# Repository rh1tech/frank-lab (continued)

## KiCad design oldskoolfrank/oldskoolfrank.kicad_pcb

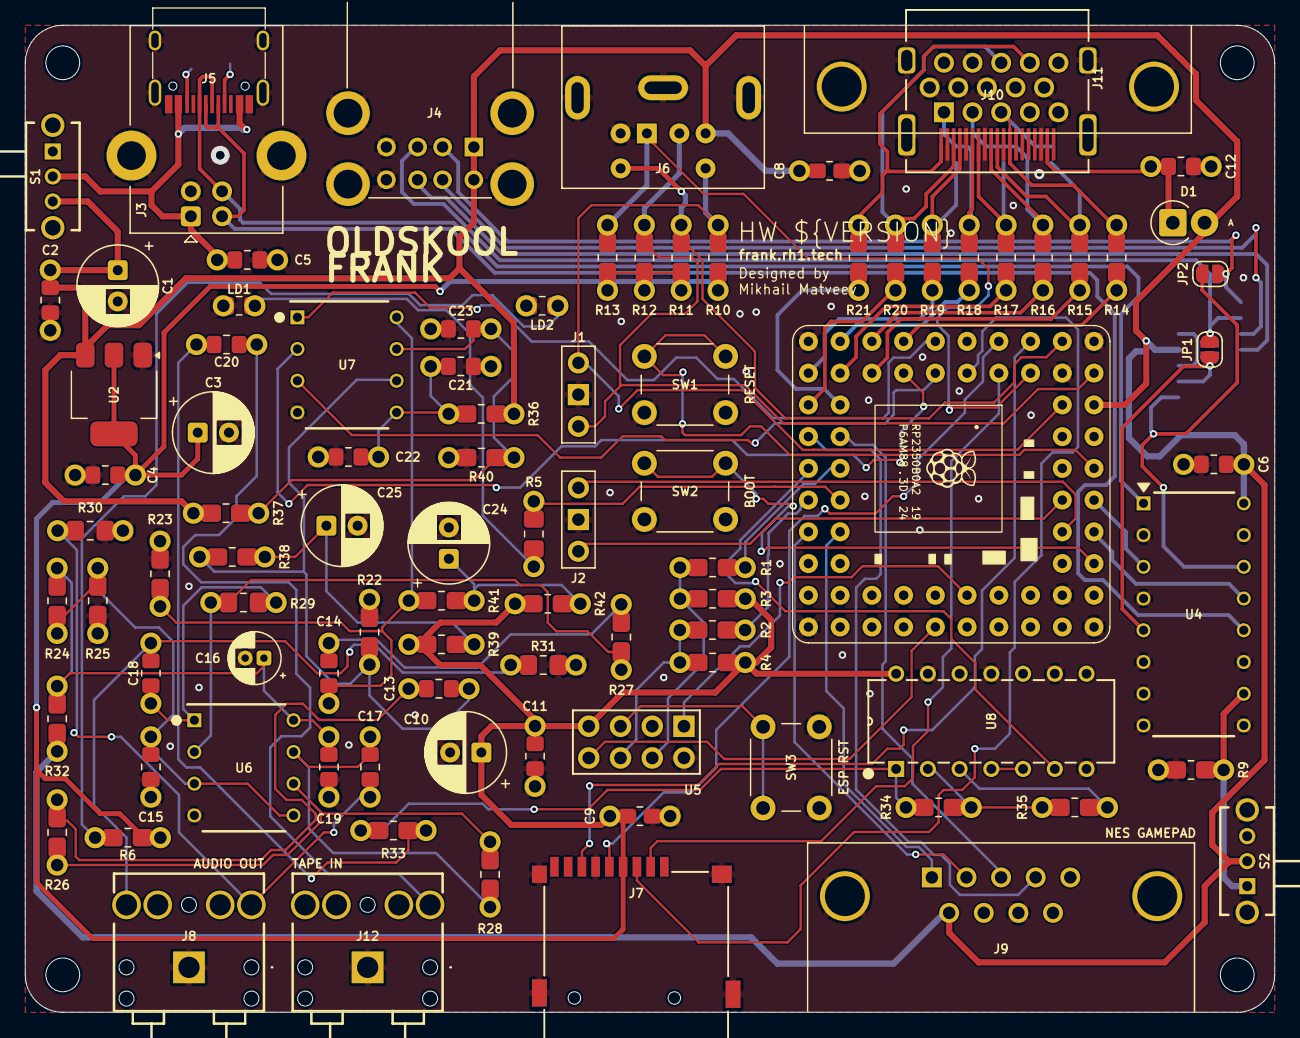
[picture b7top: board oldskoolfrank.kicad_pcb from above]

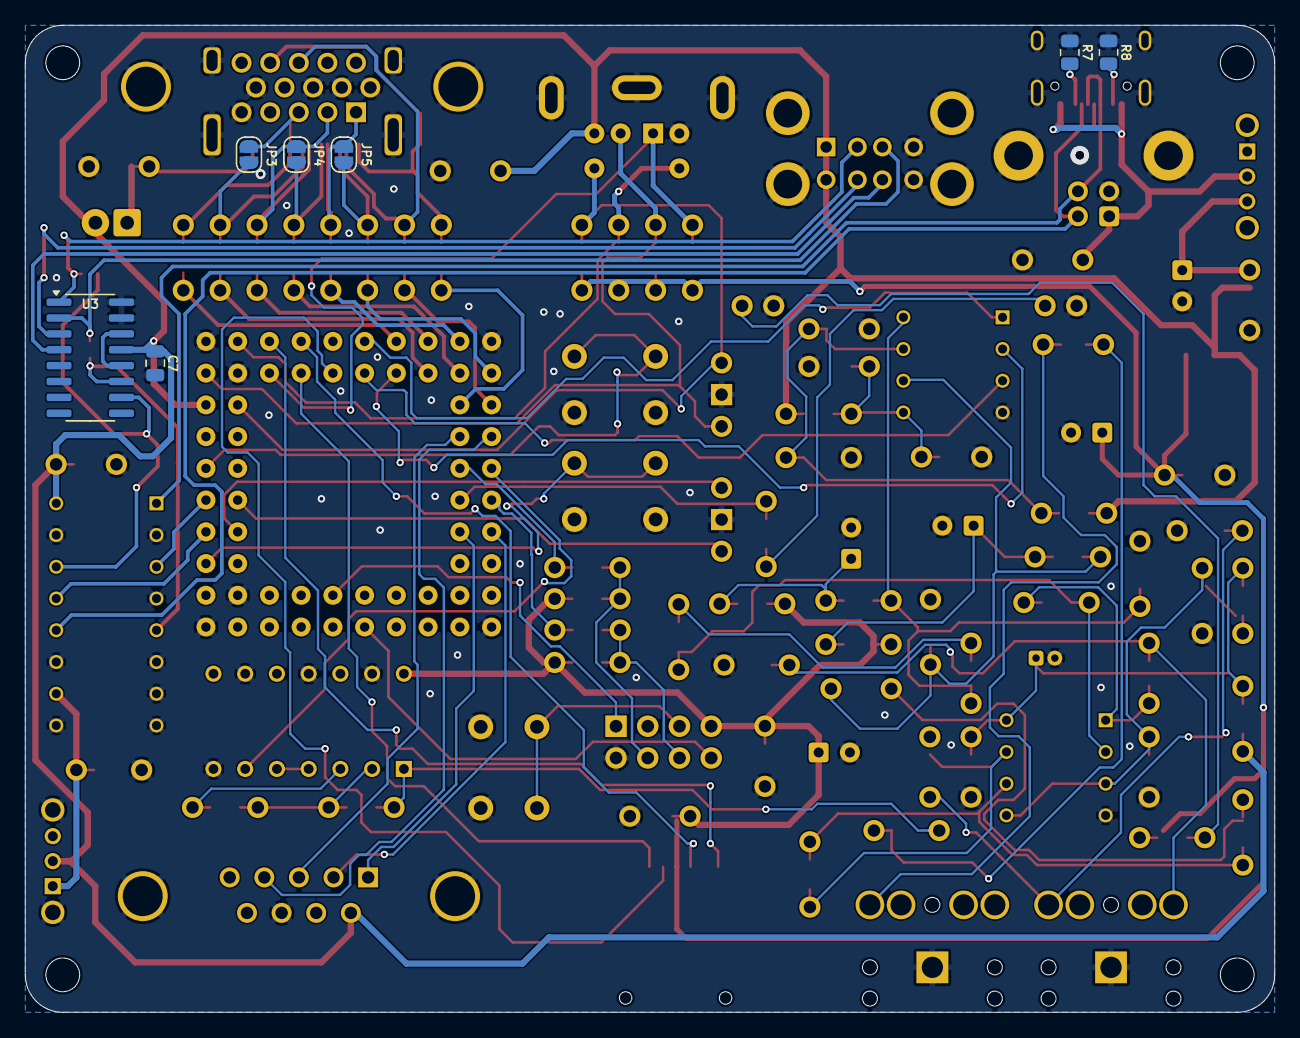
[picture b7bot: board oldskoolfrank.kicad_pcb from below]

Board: 2 copper layers, 100.0 x 79.0 mm, 104 parts (7 on the bottom side), 87 nets.

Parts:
C1, C3, C10, C24, C25: 100u; C_Radial_D6.3mm_P2.50mm
C2, C4, C6, C8, C9, C11, C12, C19, C20, C22: 100n; Combined_0805_CR
C5, C13, C14, C15, C17, C18, C21, C23: 10u; Combined_0805_CR
C7: 4.7u; C_0805_2012Metric
C16: 10u; CP_Radial_D4.0mm_P1.50mm
D1: 1N5819; D_SOD81_P2.54mm_Vertical_AnodeUp
H1, H2, H3, H4: Hole 2.7mm; MountingHole_2.7mm
J1: UART; PinSocket_1x03_P2.54mm_Vertical
J2: Debug; PinSocket_1x03_P2.54mm_Vertical
J3: USB_B; USB_B_Horizontal
J4: SS-52100-004; USB_A_Stacked
J5: USB4215-03-A; USB_C_Receptacle
J6: MDC-036; MiniDIN_6pin_Female
J7: 104031-0811; MicroSD_SMD_Long
J8: SJ1-3525N Green; AudioJack_3.5mm_SJ1-3525N_Green
J9: D-SUB 9 Male; DSUB-9_Male_TopMount
J10: DC3RX19JA2; HDMI_Female
J11: D-SUB 15 Female; DSUB-15_Female
J12: SJ1-3525N Red; AudioJack_3.5mm_SJ1-3525N_Red
JP1, JP2, JP3, JP4, JP5: Jumper (Solder); SolderJumper_2Pin
LD1: Blue; Combined_0805_LED
LD2: Green; Combined_0805_LED
R1, R2, R5, R6, R10, R11, R12, R13: 1K; Combined_0805_RE
R3, R4, R9, R24, R25, R26, R27, R40: 10K; Combined_0805_RE
R7, R8: 5.1K; R_0805_2012Metric
R14, R15, R16, R17, R18, R19, R20, R21: 220R; Combined_0805_RE
R22, R23: 2.2K; Combined_0805_RE
R28, R29: 47K; Combined_0805_RE
R30, R31: 20K; Combined_0805_RE
R32, R36, R39, R42: 100R; Combined_0805_RE
R33: 4.7K; Combined_0805_RE
R34, R35: 100K; Combined_0805_RE
R37: 51K; Combined_0805_RE
R38, R41: 470R; Combined_0805_RE
S1, S2: SK12D07VG3NS; Switch_Slide_SK12D07VG3NS
SW1: Reset; SW_PUSH_6mm_H5mm
SW2: Boot; SW_PUSH_6mm_H5mm
SW3: ESP01 Reset; SW_PUSH_6mm_H5mm
U1: Pimoroni PGA2350; PGA2350
U2: AMS1117-3.3; SOT-223-3_TabPin2
U3: MW7211A; SOP-16_3.9x9.9mm_P1.27mm
U4: 74HC4052; 74HC4052N
U5: ESP-01v090; ESP-01S
U6: LM358; DIP-8_W7.94mm_P2.54mm
U7: TDA1545A; DIP-8_W7.94mm_P2.54mm
U8: CD4069UBE

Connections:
+3V3: C3.1, C4.2, C9.2, C10.1, C11.2, J7.4 (VDD), R3.2, R4.2, R6.2, R10.2, R11.2, R12.2, R13.2, R39.1, R42.1, U2.2 (VO), U5.7 (VCC), U8.14 (VDD)
/Audio/AMP_OUTL: C17.2, J8.2 (TIP), R30.2
/Audio/AMP_OUTR: C18.2, J8.3 (RING), R31.2
/Audio/TDA_L: C13.1, R22.1, R38.2, U7.6 (IOL)
/Audio/TDA_R: C14.1, R23.1, R41.1, U7.8 (IOR)
/CDDAT3/GP5: J7.2 (DAT3/CD), U1.5 (GP5)
/CLKN/GP12: R14.2, U1.12 (GP12)
/CLKP/GP13: R15.2, U1.13 (GP13)
/CLK/GP6: J7.5 (CLK), U1.6 (GP6)
/CMD/GP7: J7.3 (CMD), U1.7 (GP7)
/D0N/GP14: R16.2, U1.14 (GP14)
/D0P/GP15: R17.2, U1.15 (GP15)
/D1N/GP16: R18.2, U1.16 (GP16)
/D1P/GP17: R19.2, U1.17 (GP17)
/D2N/GP18: R20.2, U1.19 (GP18)
/D2P/GP19: R21.2, U1.20 (GP19)
/DAT0/GP4: J7.7 (DAT0), U1.4 (GP4)
/DATA1/GP26: J9.2, U1.27 (GP26)
/DATA2/GP27: J9.1, U1.28 (GP27)
/DM: U1.53 (USB_DM), U4.13 (1Z)
/DP: U1.54 (USB_DP), U4.3 (2Z)
/EGP0/GP24: R2.2, U1.25 (GP24)
/EGP2/GP23: R1.2, U1.24 (GP23)
/ESP01S/GPIO0: R2.1, R4.1, U5.6 (GPIO0)
/ESP01S/GPIO2: R1.1, R3.1, U5.4 (GPIO2)
/J3/GP21: J9.3, U1.22 (GP21)
/J4/GP20: J9.4, U1.21 (GP20)
/KB_CLK/GP2: J6.5, R11.1, U1.2 (GP2)
/KB_DATA/GP3: J6.1, R13.1, U1.3 (GP3)
/LOAD_IN/GP22: U1.23 (GP22), U8.6 (I=*C)
/MS_CLK/GP0: J1.1, J6.6, R10.1, U1.61 (GP0)
/MS_DATA/GP1: J1.3, J6.2, R12.1, U1.62 (GP1)
/PGA2350/BOOTSEL: SW2.1, U1.51 (BOOTSEL)
/PGA2350/RUN: SW1.1, U1.56 (RUN)
/PGA2350/SWCLK: J2.3, U1.55 (SWCLK)
/PGA2350/SWDIO: J2.1, U1.52 (SWDIO)
/RX/GP38: U1.40 (GP38), U5.8 (URXD)
/TDA_DATA/GP9: U1.9 (GP9), U7.3 (DATA)
/TDA_LRCK/GP11: U1.11 (GP11), U7.2 (WS)
/TDA_SCLK/GP10: U1.10 (GP10), U7.1 (BCK)
/TX/GP39: U1.41 (GP39), U5.1 (UTXD)
/Tape In/TAPE: C20.2, J12.2 (TIP)
/USB/DI+: J3.3 (D+), J5.6 (DP1), J5.8 (DP2), U4.1 (2Y0)
/USB/DI-: J3.2 (D-), J5.5 (DN2), J5.7 (DN1), U4.12 (1Y0)
/USB/DS+: JP1.1 (A), U3.11 (DPU), U4.5 (2Y1)
/USB/DS-: JP2.1 (A), U3.10 (DMU), U4.14 (1Y1)
/USB/DU1+: J4.3 (D1+), JP1.2 (B), U3.2 (DP0)
/USB/DU1-: J4.2 (D1-), JP2.2 (B), U3.1 (DM0)
/USB/DU2+: J4.7 (D2+), U3.4 (DP1)
/USB/DU2-: J4.6 (D2-), U3.3 (DM1)
/USB/VBUS_IN: C5.1, J3.1 (VBUS), J5.2 (VBUS), J5.11 (VBUS), S1.2
/Video Out/VGA_B: J10.12 (CLKN), J11.3, JP3.1 (A), R14.1
/Video Out/VGA_BH: J10.10 (CLKP), JP3.2 (B), R15.1
/Video Out/VGA_G: J10.9 (D0N), J11.2, JP4.1 (A), R16.1
/Video Out/VGA_GH: J10.7 (D0P), JP4.2 (B), R17.1
/Video Out/VGA_HS: J10.3 (D2N), J11.13, R20.1
/Video Out/VGA_R: J10.6 (D1N), J11.1, JP5.1 (A), R18.1
/Video Out/VGA_RH: J10.4 (D1P), JP5.2 (B), R19.1
/Video Out/VGA_VS: J10.1 (D2P), J11.14, R21.1
GND: C1.2, C2.1, C3.2, C4.1, C5.2, C6.1, C7.2, C8.2, C9.1, C10.2, C11.1, C12.2, C15.1, C16.2, C19.1, C21.2, C22.2, C23.1, C24.2, C25.2, J1.2, J2.2, J3.4 (GND), J3.SH (Shield), J4.4 (GND1), J4.8 (GND2), J4.SH (Shield), J5.1 (GND), J5.12 (GND), J5.13 (SHIELD), J6.3, J7.6 (VSS), J8.1 (SLEEVE), J9.8, J10.2 (G_D2), J10.5 (G_D1), J10.8 (G_D0), J10.11 (G_CLK), J10.17 (G_DDC/CEC), J10.20 (SHIELD1), J10.21 (SHIELD2), J10.22 (SHIELD3), J10.23 (SHIELD4), J11.0, J11.5, J11.6, J11.7, J11.8, J11.10, J12.1 (SLEEVE), LD1.1 (K), LD2.1 (K), R7.1, R8.1, R9.1, R22.2, R23.2, R25.1, R30.1, R31.1, R40.1, S2.4 (MH1), S2.5 (MH2), SW1.2, SW2.2, SW3.2, U1.1 (GND), U1.18 (GND), U1.33 (GND), U1.48 (GND), U2.1 (GND), U3.15 (GND), U3.16 (GND), U4.2 (2Y2), U4.4 (2Y3), U4.6 (~E), U4.7 (VEE), U4.8 (GND), U4.9 (S1), U4.11 (1Y3), U4.15 (1Y2), U5.2 (GND), U6.4 (V-), U7.4 (GND), U8.7 (VSS), U8.9 (D14), U8.11 (E), U8.13 (F)
GP25: R5.2, U1.26 (GP25)
unnamed: C13.2, R26.2
unnamed: C14.2, R27.2
unnamed: C17.1, R28.1, U6.7
unnamed: C18.1, R29.1, U6.1
unnamed: C20.1, R33.2
unnamed: C24.1, R41.2, R42.2
unnamed: C25.1, R38.1, R39.2
unnamed: C12.1, D1.1 (K), J10.18 (+5V)
unnamed: J5.4 (CC1), R7.2
unnamed: J5.10 (CC2), R8.2
unnamed: LD1.2 (A), R5.1
unnamed: LD2.2 (A), R6.1
unnamed: U3.12 (VD33), U3.14 (VD3)
unnamed: R9.2, S2.1, U4.10 (S0)
unnamed: SW3.1, U5.5 (RST)
unnamed: C15.2, R24.1, R25.2, U6.3 (+), U6.5 (+)
unnamed: R27.1, R29.2, U6.2 (-)
unnamed: R26.1, R28.2, U6.6 (-)
unnamed: C16.1, C19.2, R24.2, R32.2, U6.8 (V+)
unnamed: C23.2, R37.2, R40.2, U7.7 (IREF)
unnamed: C21.1, C22.1, R36.1, U7.5 (VDD)
unnamed: R33.1, R34.2, U8.1 (A)
unnamed: R35.1, U8.3 (B)
unnamed: U8.4 (H=*B), U8.5 (C)
unnamed: R34.1, R35.2, U8.2 (G-*A)
VBUS: C1.1, C2.2, C6.2, C7.1, C8.1, D1.2 (A), J4.1 (VBUS1), J4.5 (VBUS2), J6.4, J9.6, R32.1, R36.2, R37.1, S1.3, S2.2, U1.60 (VBUS), U2.3 (VI), U3.13 (VDD5), U4.16 (VCC)
